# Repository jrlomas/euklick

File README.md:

# Euklick BETA

Single PCB 5V optical probe for 3D printers.  Euklick is meant to work with the new Omron optical microswitches of the [D2FP series](https://www.mouser.com/datasheet/2/307/Omron_08182023_D2FP_Datasheet_English-3305532.pdf), specifically the [D2FP-FN2](https://www.mouser.com/ProductDetail/653-D2FP-FN2).  This switch is rated to a *minimum* of **70,000,000** operations, and much tighter tolerances at the time the switch is pressed.

# The PCB, standing on the shoulder of giants
The PCB borrows, known euphemistically in the music industry as *sampling*, from the designs of the Euclid probe and PCBKlicky.  Unlike PCBKlicky, however, to lower the cost and streamline ordering boards from manufacturers, it makes use of a single board that can be used for both the microswitch (probe), and toolhead side.  Although not necessary, when the board is used in its toolhead holder, the wings / leaves at the end of the board can be snapped as to provide a tighter fit to the plastic parts.  There are cutouts and mouse bites that make it possible to snap the ends, with some force.  The board is mostly compatible with PCBKlicky; nonetheless, the switch is slightly offset from the centerline of the PCB since the pinout for the optical switch changed from the inline package of the older D2F physical switches.  This change makes it possible for the mounted magnets to avoid the soldering pads of the optical switch, while re-using the original magnet positions.
Unlike PCBKlicky, the board only supports 5V as its source of power, and power is not optional (since the optical switch requires active power).

# BOM

| Item | Quantity | Notes |
| ----------- | ------------ | ----------- |
| toolhead PCB | 2 | [gerber files](euklick_production/euklick.zip), [bom](euklick_production/bom.csv), and [cpl](euklick_production/positions.csv) files to order |
| 1K 0850 Resistor | 1 ||
| 20k 0850 Resistor | 1|  Pull-up resistor any value between 10k and 50k|
| 680R 0805 Resistor | 1 | LED resistor |
| 0805 LED | 1 | Any color of your choice |
| JST-XH 3 pin header | 1 | |
| JST-XH 3 wire pigtail connector | 1| |
| pair of countersunk, matching magnets | 5 | [source](https://www.kjmagnetics.com/proddetail.asp?prod=R422CS-P&cat=15)|
| M2x3.2x4mm heatset inserts | 10 | |
| Omron D2FP-FN2 optical switch | 1 | [source](https://www.mouser.com/ProductDetail/653-D2FP-FN2)|
| Self-tapping stainless torx drive M2 screws | 3 | |
| M3x6mm flat head screws | 2 | |

# Assembly

Two of the boards have to be used for assembly.
For the upper board (board attach to the toolhead), only the JST 3 pin header is necessary, along with three countersunk magnets.  Optionally, the *wings* on the board can be snapped along the provided mouse bites line.

For the lower board the switch should be attached from the side marked S1 as here, and the rear of the board should be populated

# License
Free for personal non-comercial use, see the [license](LICENSE.md).  I am [knight_rad.iant](https://discord.com/users/1038855498696499321) on Discord.

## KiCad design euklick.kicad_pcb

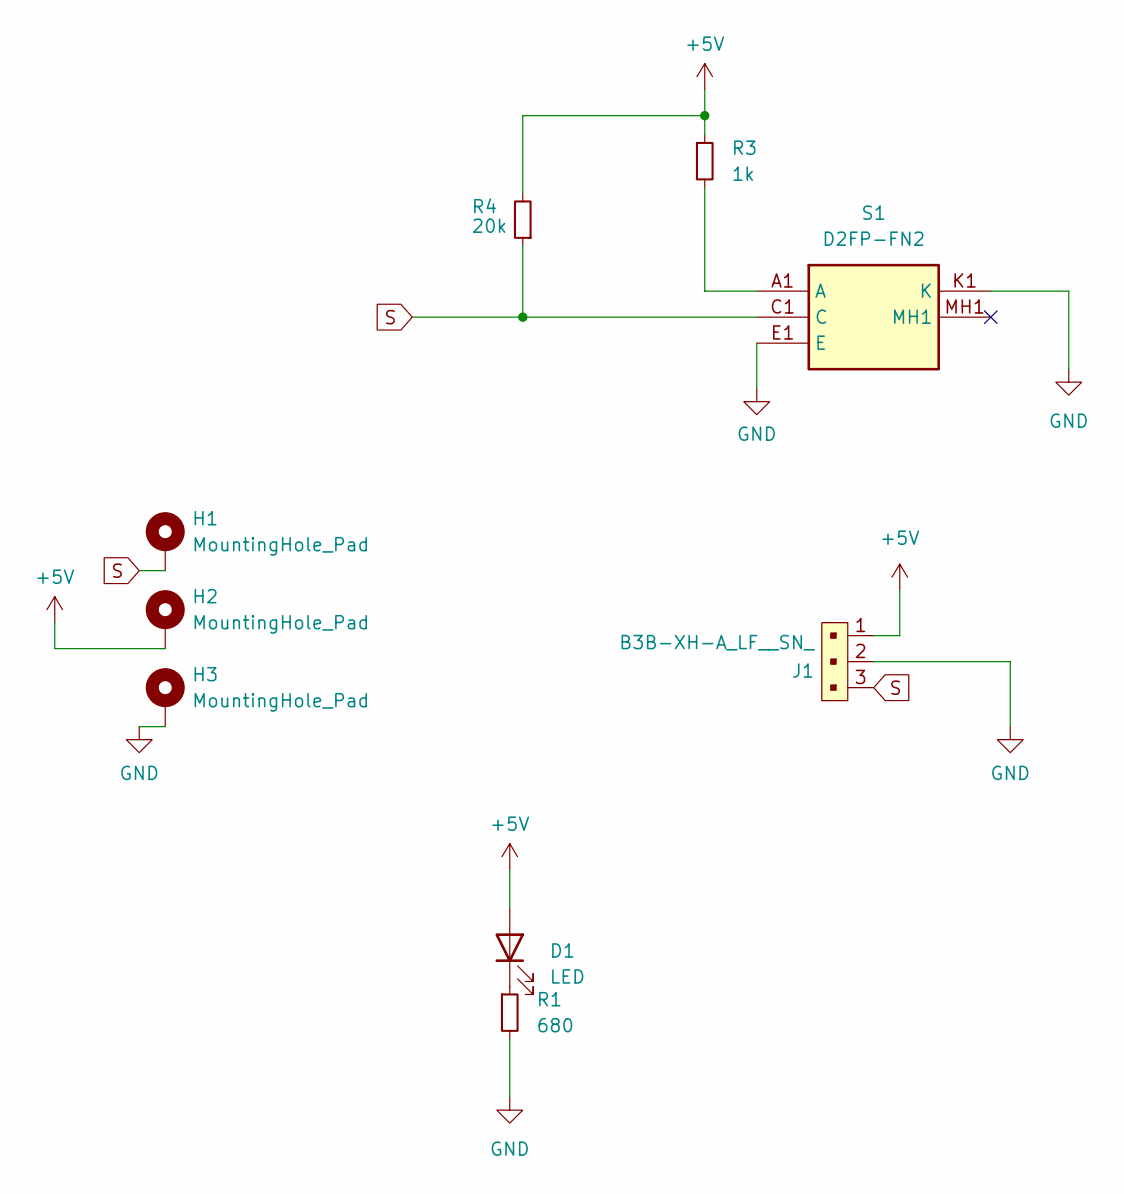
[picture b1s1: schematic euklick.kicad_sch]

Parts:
D1: LED; LED_0805_2012Metric_Pad1.15x1.40mm_HandSolder; LCSC Part C84256
H1, H2, H3: MountingHole_Pad; MountingHole_2.7mm_Pad
J1: B3B-XH-A_LF__SN_; JST_XH_B3B-XH-A_1x03_P2.50mm_Vertical; MPN B3B-XH-A(LF)(SN); Digi-Key_PN 455-2248-ND
R1: 680; R_0805_2012Metric_Pad1.20x1.40mm_HandSolder
R3: 1k; R_0805_2012Metric_Pad1.20x1.40mm_HandSolder
R4: 20k; R_0805_2012Metric_Pad1.20x1.40mm_HandSolder
S1: D2FP-FN2; D2FPFN2; Manufacturer_Part_Number D2FP-FN2

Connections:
+5V: D1.2 (A), H2.1, J1.1, R3.1, R4.2
GND: H3.1, J1.2, R1.2, S1.E1 (E), S1.K1 (K)
unnamed: D1.1 (K), R1.1
unnamed: R3.2, S1.A1 (A)
S: H1.1, J1.3, R4.1, S1.C1 (C)

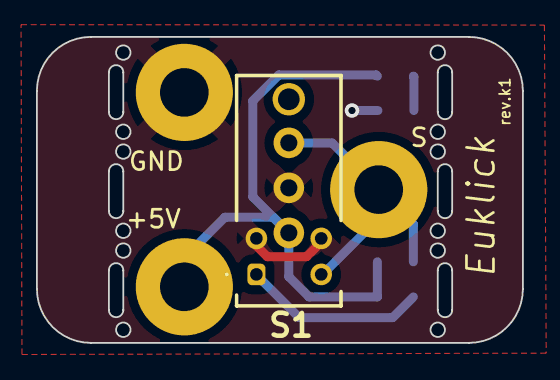
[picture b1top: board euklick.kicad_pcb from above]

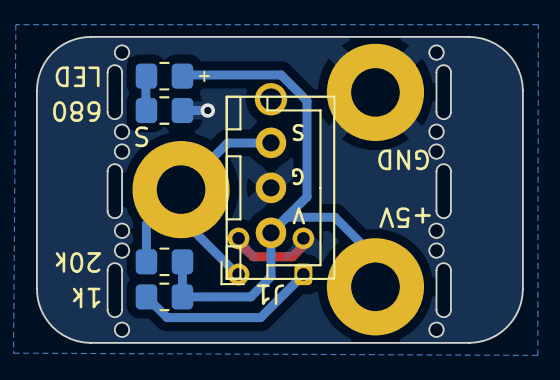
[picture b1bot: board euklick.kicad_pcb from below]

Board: 2 copper layers, 27.0 x 17.0 mm, 9 parts (5 on the bottom side), 5 nets.

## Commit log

2023-10-13 Create LICENSE
2023-10-13 Rename LICENSE to LICENSE.md
2023-10-13 Initial working commit
2023-10-13 New instructions
2023-10-13 added Gerbers for production and updated readme
2023-10-13 Updated BOM in README to include resistors and led
2023-10-13 Corrected typo
2023-10-13 another typo slayed
